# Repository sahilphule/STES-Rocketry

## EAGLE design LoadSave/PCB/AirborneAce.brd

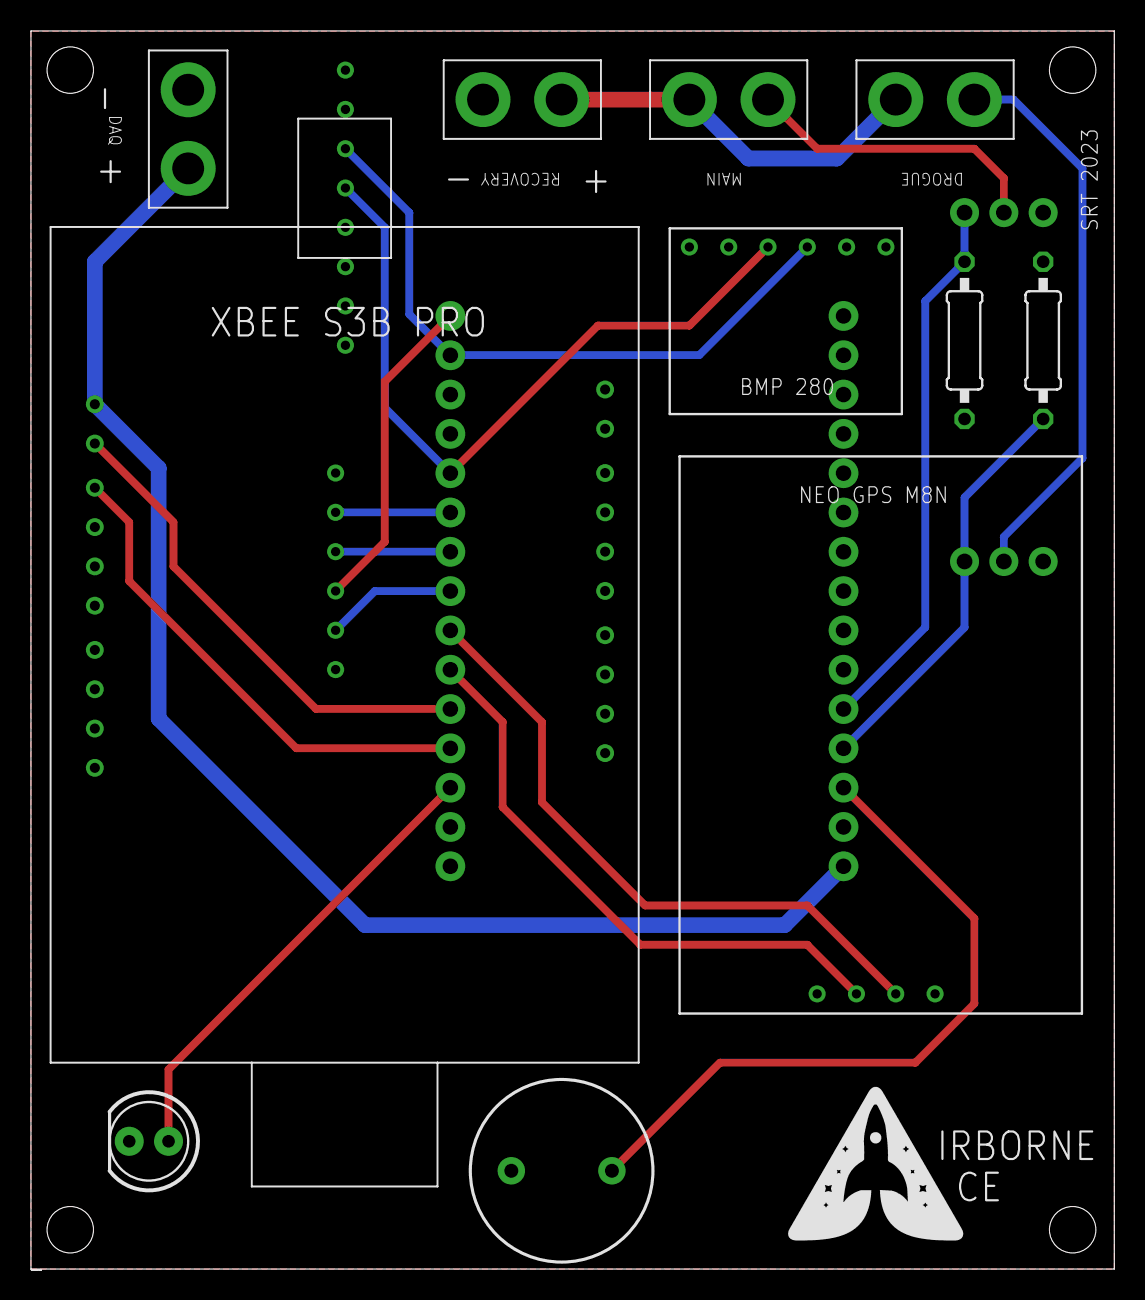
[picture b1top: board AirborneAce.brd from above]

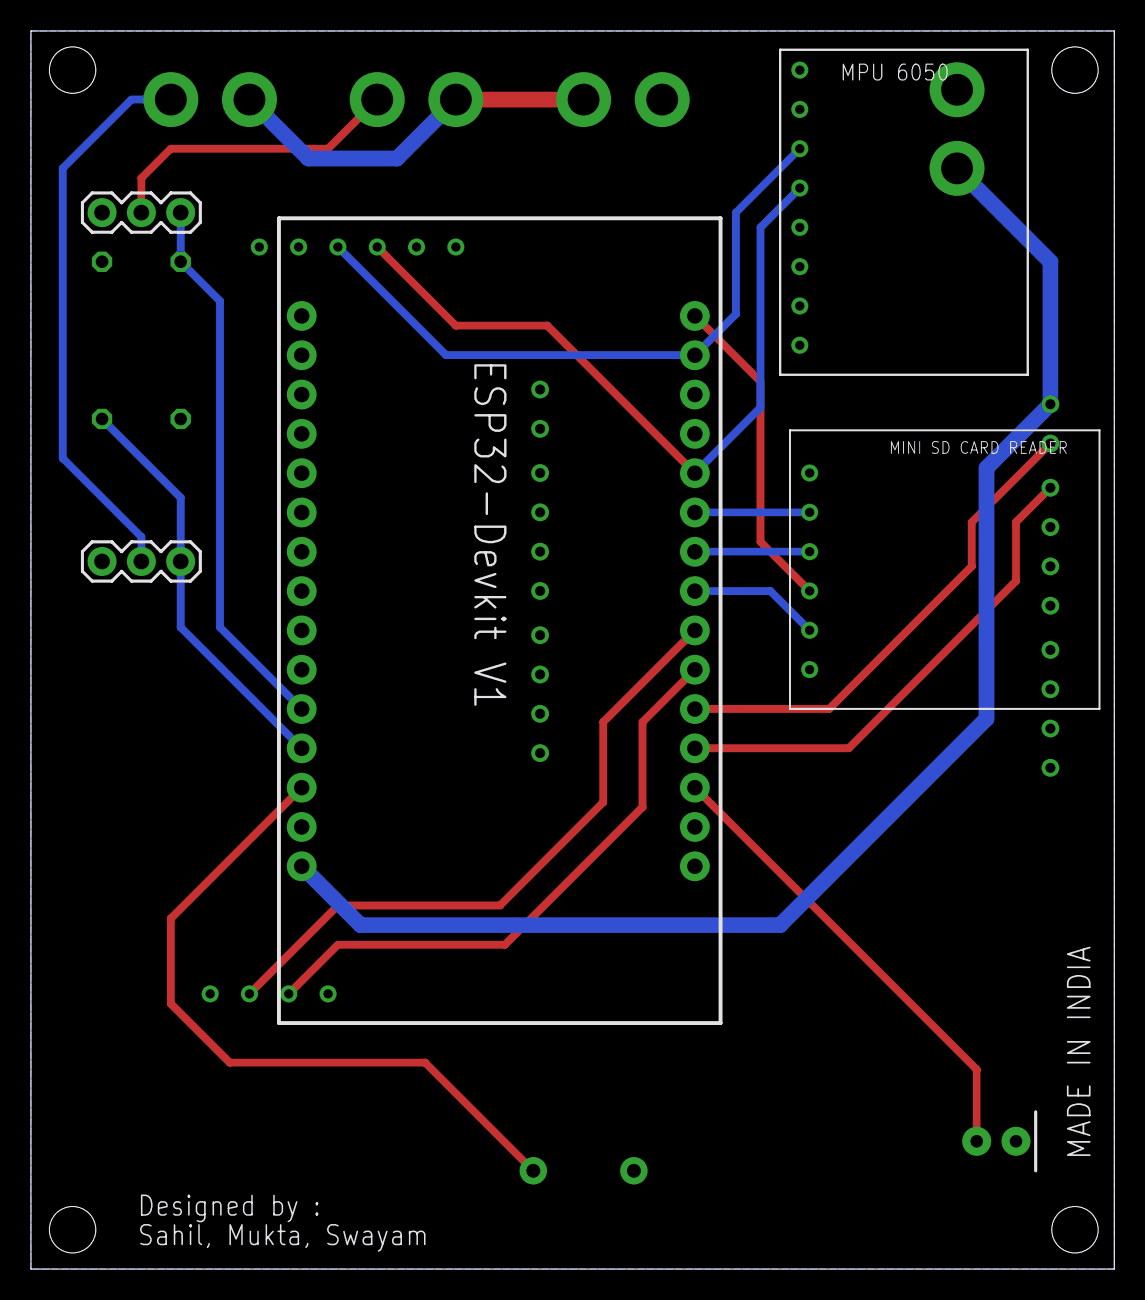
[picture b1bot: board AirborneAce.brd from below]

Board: 2 copper layers, 70.0 x 80.0 mm, 16 parts (5 on the bottom side), 20 nets.

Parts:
D1: LED_5MM
J1, J2, J3, J8: 1X02_XTRA_BIG
J6, J7: 455-1750-1-ND; 1X03
LS1: BUZZER-PTH; BUZZER-12MM
R3, R4: 0207/10
U$1: NEWMPU6050NEWMPU6050; 6050
U$2: ESP32DEVKITV1; ESP32-DEVKITV1
U$3: NEOGPSM8NNEOGPSM8N; NEOGPSM8N
U$4: BMP280BMP280; BMP280
U$5: MINISD; MNISD
U$6: XBEES3BXBEES3B; XBEES3BPRO

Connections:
3V: U$1.VCC, U$2.3V3, U$3.VCC, U$4.VCC, U$5.3V3
BUZZER: LS1.+, U$2.D13
CLK: U$2.D18, U$5.SCK
CS: U$2.D5, U$5.CS
DROGUE: J6.3, R3.2, U$2.D12
GND: D1.K, J1.2, J2.2, J6.1, J7.1, LS1.-, R3.1, R4.1, U$1.GND, U$2.GND@1, U$2.GND@2, U$3.GND, U$4.GND, U$5.GND, U$6.GND
GPS_RX: U$2.D17, U$3.RX
GPS_TX: U$2.D16, U$3.TX
LED: D1.A, U$2.D15
MAIN: J7.3, R4.2, U$2.D14
MISO: U$2.D19, U$5.MISO
MOSI: U$2.D23, U$5.MOSI
NICHROME: J1.1, J3.1, J8.1
SCL: U$1.SCL, U$2.D22, U$4.SCL
SDA: U$1.SDA, U$2.D21, U$4.SDA
TERMINAL1: J3.2, J6.2
TERMINAL2: J7.2, J8.2
VIN: J2.1, U$2.VIN, U$6.3V3
XBEE_RX: U$2.D2, U$6.RX
XBEE_TX: U$2.D4, U$6.TX

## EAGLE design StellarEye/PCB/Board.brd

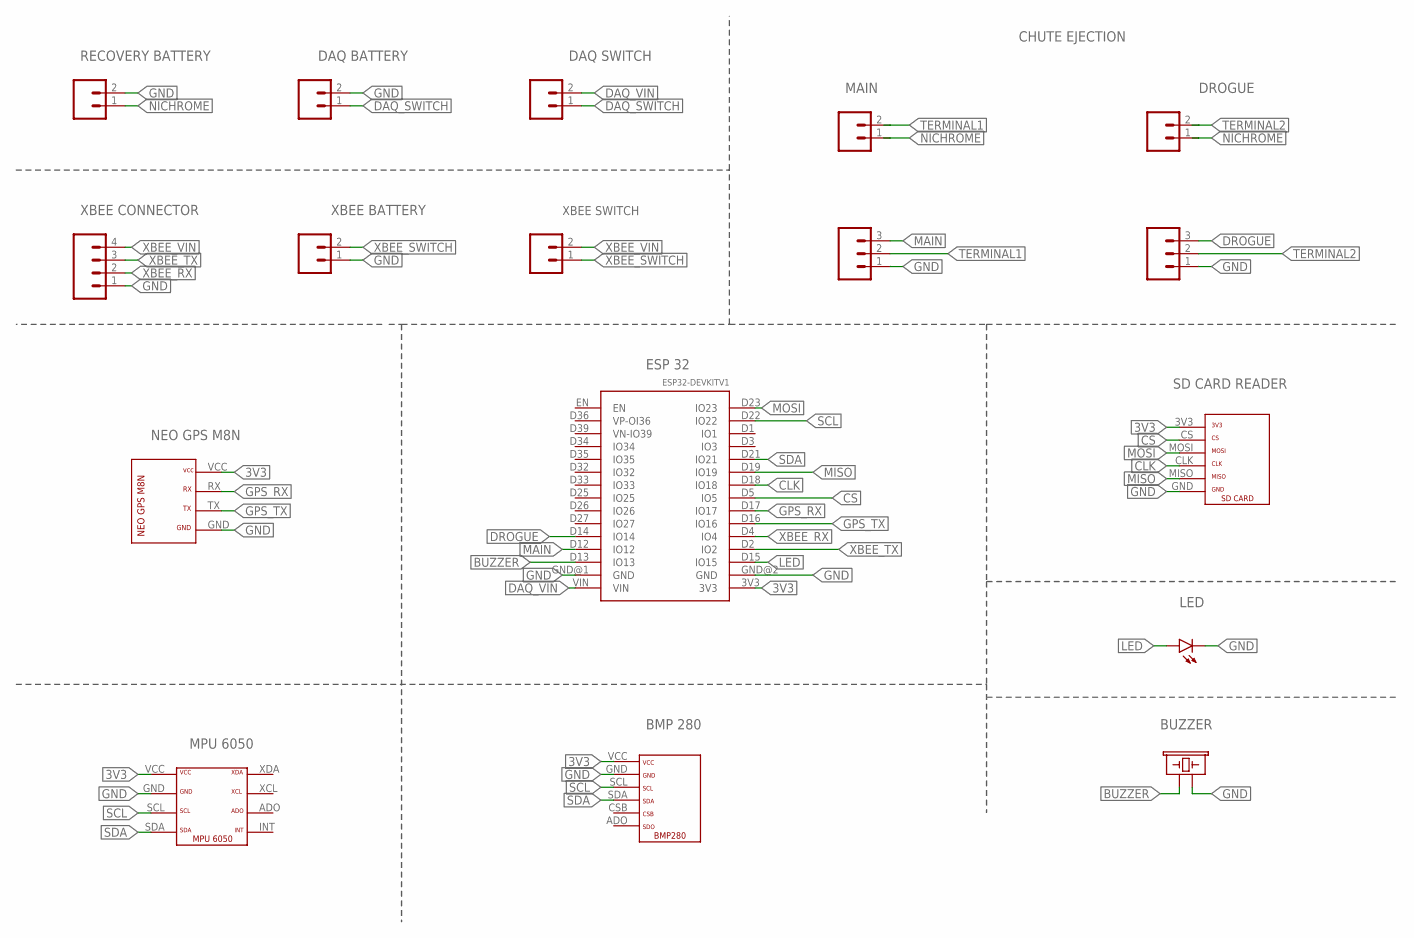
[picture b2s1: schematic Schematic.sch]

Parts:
J1, J2: 455-1750-1-ND; 1X03
J8, J12, J13, J14, J15, J16, J17: CONN_02PTH4; 1X02_XTRA_BIG
J11: CONN_04PTH; 1X04
LED1: LED5MM
LS1: BUZZER-PTH; BUZZER-12MM
U$1: ESP32DEVKITV1; ESP32-DEVKITV1
U$2: BMP280
U$3: MINISD
U$4: MPU6050
U$5: NEOM8N; NEOM8M

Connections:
3V3: U$1.3V3, U$2.VCC, U$3.3V3, U$4.VCC, U$5.VCC
BUZZER: LS1.+ (1), U$1.D13 (IO13)
CLK: U$1.D18 (IO18), U$3.CLK
CS: U$1.D5 (IO5), U$3.CS
DAQ_SWITCH: J12.1, J13.1
DAQ_VIN: J13.2, U$1.VIN
DROGUE: J1.3, U$1.D14 (IO14)
GND: J1.1, J2.1, J8.2, J11.1, J12.2, J15.1, LED1.K (C), LS1.- (2), U$1.GND@1 (GND), U$1.GND@2 (GND), U$2.GND, U$3.GND, U$4.GND, U$5.GND
GPS_RX: U$1.D17 (IO17), U$5.RX
GPS_TX: U$1.D16 (IO16), U$5.TX
LED: LED1.A, U$1.D15 (IO15)
MAIN: J2.3, U$1.D12 (IO12)
MISO: U$1.D19 (IO19), U$3.MISO
MOSI: U$1.D23 (IO23), U$3.MOSI
NICHROME: J8.1, J16.1, J17.1
SCL: U$1.D22 (IO22), U$2.SCL, U$4.SCL
SDA: U$1.D21 (IO21), U$2.SDA, U$4.SDA
TERMINAL1: J2.2, J16.2
TERMINAL2: J1.2, J17.2
XBEE_RX: J11.2, U$1.D4 (IO4)
XBEE_SWITCH: J14.1, J15.2
XBEE_TX: J11.3, U$1.D2 (IO2)
XBEE_VIN: J11.4, J14.2

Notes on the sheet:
RECOVERY BATTERY
DAQ BATTERY
XBEE BATTERY
XBEE SWITCH
DAQ SWITCH
XBEE CONNECTOR
NEO GPS M8N
ESP 32
MPU 6050
BMP 280
SD CARD READER
LED
BUZZER
MAIN
DROGUE
CHUTE EJECTION

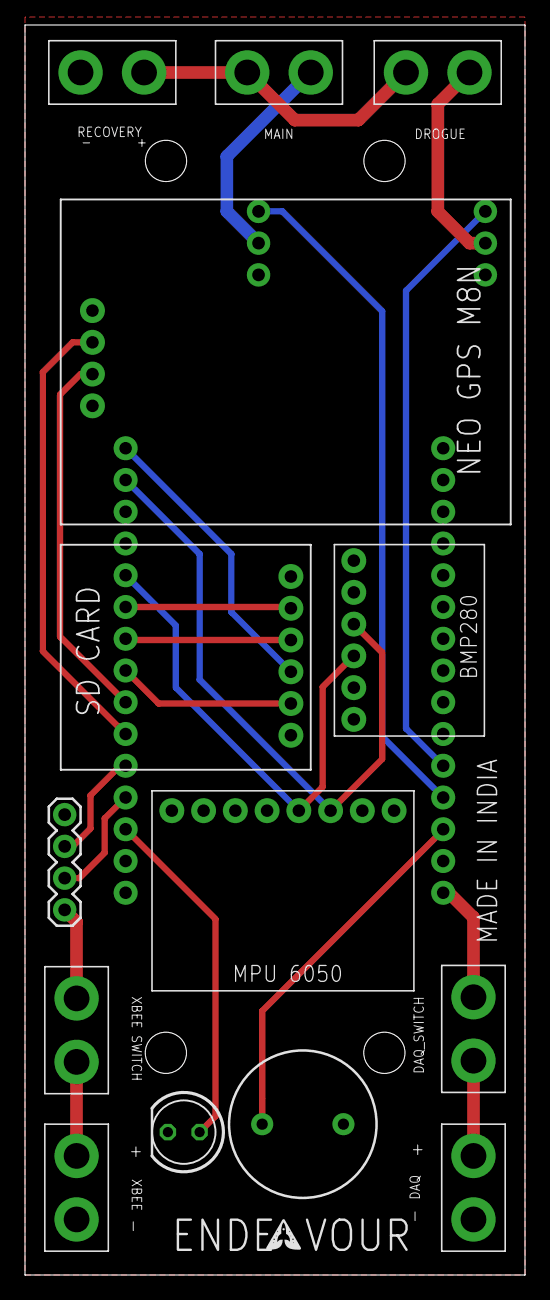
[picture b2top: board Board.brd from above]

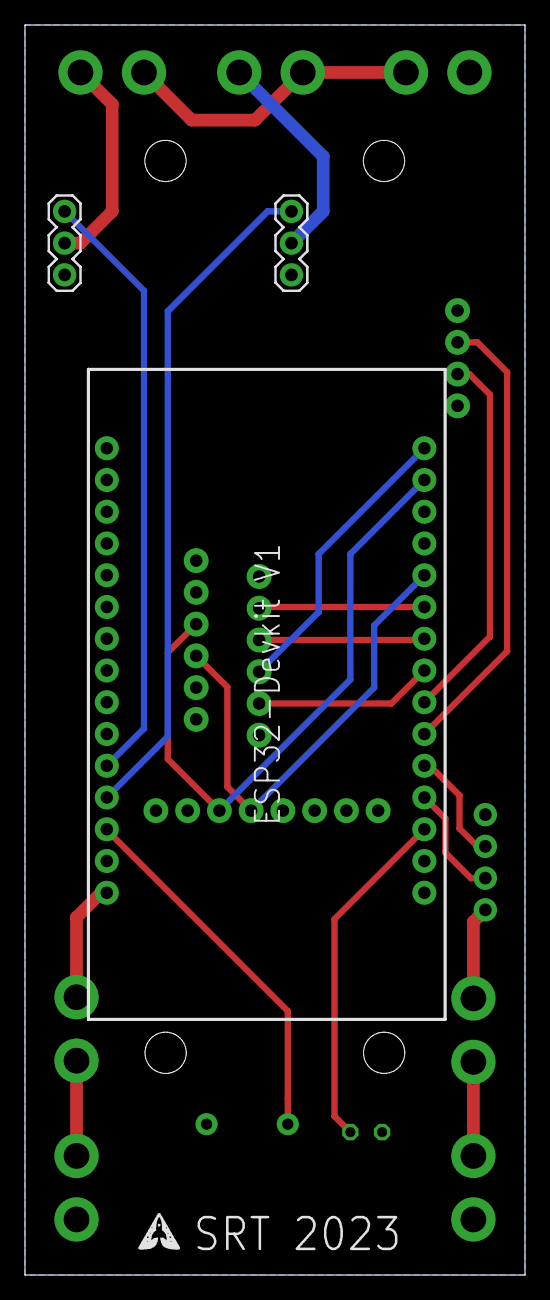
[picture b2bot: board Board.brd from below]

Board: 2 copper layers, 40.0 x 100.0 mm, 17 parts (3 on the bottom side), 23 nets.

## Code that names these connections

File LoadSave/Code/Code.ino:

#include <SD.h>
#include <SPI.h>
#include <Adafruit_Sensor.h>
#include <Adafruit_BMP280.h>
#include <Adafruit_MPU6050.h>
#include <Wire.h>
#include <TinyGPSPlus.h>

Adafruit_BMP280 bmp;
Adafruit_MPU6050 mpu;
TinyGPSPlus gps;
File myFile;

const int CS=5,n=15;
int buzzer=13,led=15,drogue_pin=12,main_pin=14,loopDelay=200;
String dataFile="/data.txt",logFile="/log.txt";
bool flag_drogue=false,flag_main=false;
float sec=0.00000,pressure,curr_altitude,temperature,last_altitude,latitude,longitude,acceleration_x,acceleration_y,acceleration_z,rotation_x,rotation_y,rotation_z,apogee,avg=0,drogue_altitude,main_altitude,location_altitude;

void setup() {

  pinMode(buzzer,OUTPUT);
  pinMode(led,OUTPUT);
  pinMode(drogue_pin,OUTPUT);
  pinMode(main_pin,OUTPUT);

  digitalWrite(buzzer,LOW);
  digitalWrite(led,LOW);
  digitalWrite(drogue_pin,LOW);
  digitalWrite(main_pin,LOW);

  Serial.begin(9600);
  Serial2.begin(9600,SERIAL_8N1,16,17);
  
  delay(5000);

  if(SD.begin(CS)){
    Serial.println("SD initialized successfully! \n");
    digitalWrite(buzzer,HIGH);
    digitalWrite(led,HIGH);
    delay(1000);
    digitalWrite(led,LOW);
    digitalWrite(buzzer,LOW);
  }
  else{
    Serial.println("Error initializing SD! \n");
    while(1){

    }
  }  

  if(SD.exists(dataFile)){
    Serial.println("Deleting the data file! \n");
    SD.remove(dataFile);
  }

  if(SD.exists(logFile)){
    Serial.println("Deleting the log file! \n");
    SD.remove(logFile);
  }

  delay(1000);
  
  myFile=SD.open(logFile,FILE_APPEND);
  
  if(myFile){
    
    Serial.println("Time(s),Pressure(Pa),Altitude(ft),Temperature(C),Latitude(deg),Longitude(deg),Acceleration_x(m/s2),Acceleration_y(m/s2),Acceleration_z(m/s2),Rotation_x(deg),Rotation_y(deg),Rotation_z(deg) \n");
    myFile.println("Time(s),Pressure(Pa),Altitude(ft),Temperature(C),Latitude(deg),Longitude(deg),Acceleration_x(m/s2),Acceleration_y(m/s2),Acceleration_z(m/s2),Rotation_x(deg),Rotation_y(deg),Rotation_z(deg) \n");
    
    if(bmp.begin(0x76)){
      Serial.println("BMP initialized successfully! \n");
      myFile.println("BMP initialized successfully! \n");
      
      digitalWrite(buzzer,HIGH);
      digitalWrite(led,HIGH);
      delay(1000);
      digitalWrite(led,LOW);
      digitalWrite(buzzer,LOW);
    }
    else{
      Serial.println("Error initializing BMP! \n");
      myFile.println("Error initializing BMP! \n");
      while(1){
      
      }
    }
    
    delay(1000);
    
    if(mpu.begin(0x68)){
      Serial.println("MPU initialized successfully! \n");
      myFile.println("MPU initialized successfully! \n");

      digitalWrite(buzzer,HIGH);
      digitalWrite(led,HIGH);
      delay(1000);
      digitalWrite(led,LOW);
      digitalWrite(buzzer,LOW);

      mpu.setAccelerometerRange(MPU6050_RANGE_8_G);
      mpu.setGyroRange(MPU6050_RANGE_500_DEG);
      mpu.setFilterBandwidth(MPU6050_BAND_21_HZ);
    }
    else{
      Serial.println("Error initializing MPU! \n");
      myFile.println("Error initializing MPU! \n");
      while(1){
        
      }
    }

    myFile.close();
  }
  

  else{
    Serial.println("Error opening file in setup! \n");
    while(1){

    }
  }    

}

void loop() {

  myFile=SD.open(dataFile,FILE_APPEND);
  
  if(myFile){
    digitalWrite(led,HIGH);
    getBmpData();
    getGpsData();
    getMpuData();
    myFile.close();
    digitalWrite(led,LOW);
    sec=sec+loopDelay;
  }
  else{
    Serial.println("Error opening data file! \n");
    while(1){
      
    }
  }

  if(!flag_drogue){
    drogue_func();
  }

  if(flag_drogue==true && flag_main==false){
    main_func();    
  }

  delay(loopDelay);
}


void getBmpData(){
  last_altitude=curr_altitude;
  pressure=bmp.readPressure();
  curr_altitude=bmp.readAltitude()*3.28084;
  temperature=bmp.readTemperature();

  Serial.print(sec);
  Serial.print(",");
  Serial.print(pressure);
  Serial.print(",");
  Serial.print(curr_altitude);
  Serial.print(",");
  Serial.print(temperature);
  Serial.print(",");

  myFile.print(sec);
  myFile.print(",");
  myFile.print(pressure);
  myFile.print(",");
  myFile.print(curr_altitude);
  myFile.print(",");
  myFile.print(temperature);
  myFile.print(",");
}


void getGpsData(){
  
  while(Serial2.available()>0){
    if(gps.encode(Serial2.read())){
      if(gps.location.isValid()){
        latitude=gps.location.lat();
        longitude=gps.location.lng();
      }
    }
  } 

  Serial.print(latitude,6);
  Serial.print(",");
  Serial.print(longitude,6);
  Serial.print(",");

  myFile.print(latitude,6);
  myFile.print(",");
  myFile.print(longitude,6);
  myFile.print(",");
}


void getMpuData(){
  
  sensors_event_t a,g,temp;
  mpu.getEvent(&a,&g,&temp);
  
  acceleration_x=a.acceleration.x;
  acceleration_y=a.acceleration.y;
  acceleration_z=a.acceleration.z;
  
  rotation_x=g.gyro.x;
  rotation_y=g.gyro.y;
  rotation_z=g.gyro.z;

  Serial.print(acceleration_x);
  Serial.print(",");
  Serial.print(acceleration_y);
  Serial.print(",");
  Serial.print(acceleration_z);
  Serial.print(",");
  Serial.print(rotation_x);
  Serial.print(",");
  Serial.print(rotation_y);
  Serial.print(",");
  Serial.println(rotation_z);
  
  myFile.print(acceleration_x);
  myFile.print(",");
  myFile.print(acceleration_y);
  myFile.print(",");
  myFile.print(acceleration_z);
  myFile.print(",");
  myFile.print(rotation_x);
  myFile.print(",");
  myFile.print(rotation_y);
  myFile.print(",");
  myFile.println(rotation_z);
}


void drogue_func(){  

  if(curr_altitude<last_altitude){
    apogee=last_altitude;
            
    for(int i=0;i<n;i++){
      avg=avg+(curr_altitude-last_altitude);       
      getBmpData();
      delay(200);
    }

    myFile=SD.open(logFile,FILE_APPEND);

  
    myFile.println("Trigger 1 triggered!");
    avg=avg/n;
        
    if(int(avg)<0){
      myFile.printf("Apogee : %d ft \n",apogee);
      myFile.println("Trigger 2 triggered!");
      
      drogue_altitude=curr_altitude;
      
      digitalWrite(buzzer,HIGH);
      digitalWrite(drogue_pin,HIGH);
      delay(5000);
      digitalWrite(drogue_pin,LOW);
      digitalWrite(buzzer,LOW);

      flag_drogue=true;
      myFile.printf("Drogue parachute deployed at : %d ft \n",drogue_altitude);
    }
    else{
      avg=0;
    }
    myFile.close();      
  }    
}

void main_func(){
  
  myFile=SD.open(logFile,FILE_APPEND);
  
  if(curr_altitude<=(location_altitude + 1500)){
    myFile.println("Trigger 3 triggered! \n");
    
    main_altitude=curr_altitude;

    digitalWrite(buzzer,HIGH);
    digitalWrite(main_pin,HIGH);
    delay(5000);
    digitalWrite(main_pin,LOW);
    digitalWrite(buzzer,LOW);

    flag_main=true;
    myFile.printf("Main parachute deployed at : %d ft \n",main_altitude);
    myFile.close();
  }
}

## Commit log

2024-06-01 added files

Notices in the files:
parts and their libraries:
SparkFun-LED: Licensing: Creative Commons ShareAlike 4.0 International - https://creativecommons.org/licenses/by-sa/4.0
